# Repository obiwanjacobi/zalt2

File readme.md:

# Zalt II

The design of the Zalt II computer hinges on a 10-slot (PC) ISA powered backplane I had laying around.

So all modules have an ISA edge connector and although the physical construction is the same as the (PC) ISA bus, the electrical connections are different. So don't try plugging the modules into an old PC.

All card modules (except the Main Board) represent a "smart device".
A smart device has it's own processor to give it additional functionality and perform DMA to offload the CPU.

## Main Board v2.0 (manufactured)

The "motherboard" of the Zalt II computer, containing the 20MHz Z80 CPU, a CPLD for condensed system logic (like MMU/MPU) and an MCU for some (serial) peripherals.

---

## Mass Storage Card

> TBD

- Support IDE hard disks / Compact Flash
- Support File System (FAT16/32)
- Efficient file data transfer (DMA and prefetch)

---

## Video Display Card

> TBD

Currently being researched.

We start of with a simple test on an (SSD1963) [LCD display](./Lcd%20display.md) I have.

- command-based interaction
- lots of graphic services (layers, sprites, transformations, animation, scrolling)
- Additional memory for storing graphic assets
- maybe even a built-in windowing system
- VGA and HDMI using a CPLD to do the heavy lifting
- MCU (STM32?) for 'accelerion', additional memory and DMA

---

## Audio Interface Card

> TBD

Fague ideas on what to do here.

- use MIDI (files) to drive the sound generator(s).
- use a teensy and the audio library (design) capabilities as the processor / sound generator.
- Allow samples to be uploaded and played.
- Prepare for recording audio samples (don't make it impossable), but no plans to use it.

---

## Network Card

> TBD

No idea yet how to do this, but seems like a good idea.

- LAN + WIFI (+BLE?)
- W5500 LAN module (AliExpress)

---

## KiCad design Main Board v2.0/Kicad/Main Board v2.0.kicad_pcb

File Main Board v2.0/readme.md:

# Zalt 2

Version 2 of the Zalt homebrew Z80 computer.

## Z80 CPU

The main board runs a 20MHz Z80.

It contains a 512kB ROM and a 512kB RAM.

## Memory Management Unit

- `Page`: a block of 4k of  physical memory that can be freely mapped into the CPU address space.
- `Page Id` (0-8192) an identifier for a memory page from physical memory.
- `Page Index` (0-15) a location for each of the 16 (active) CPU memory pages.
- `Bank`: A collection of assigned `Page Id`s for all `Page Index`es. Only one bank is active at a time and it defines what physical memory pages are visible to the CPU.
- `Bank Id` (0-32): a stack of max 32 banks that are available to the program/task.
- `Map Id` (0-64): allows each task (as in multi-tasking) to have their private stack of (32) banks.

> The ratio between available Bank-Ids and Map-Ids can be changed later if needed.

### Memory Bank Mapping

The CPU memory address is mapped by the MMU to one of the memory pages in physical memory.
This takes the hi-nible of the CPU address to index the lookup table and produce the physical memory address.
Besides the memory address bits, the lookup table also outputs memory-protection bits for each page.

The values in the lookup table can be programmed, thus changing the pages pointed to in the specific page-index locations.

The OS forces one (or more) -at $000- page-index locations to be present in all memory banks.
This ensures that basic machinery for the OS is always accessible for each application memory configuration.

One 4k block of ROM contains only $FF's (RST38). RST38 is a trap instruction to (try to) catch run-away code.
This can be used to map into page-index's where no valid memory is to be configured.

Refer to the OS's [program loader](<./Source/CPU/Program Loader.md>) for more detail on how the 16 page-indexes are allocated.

## Expansion Bus

We are using a powered ISA backplane to make this a modular system.

> After some research I found the goal to keep the ISA bus ISA-compatible -that it would run original PC ISA-cards- to be a great burdon and compilcate the design unnecessary.

This expansion bus definition is different from the (PC) ISA definition, only the Power pins are kept the same.

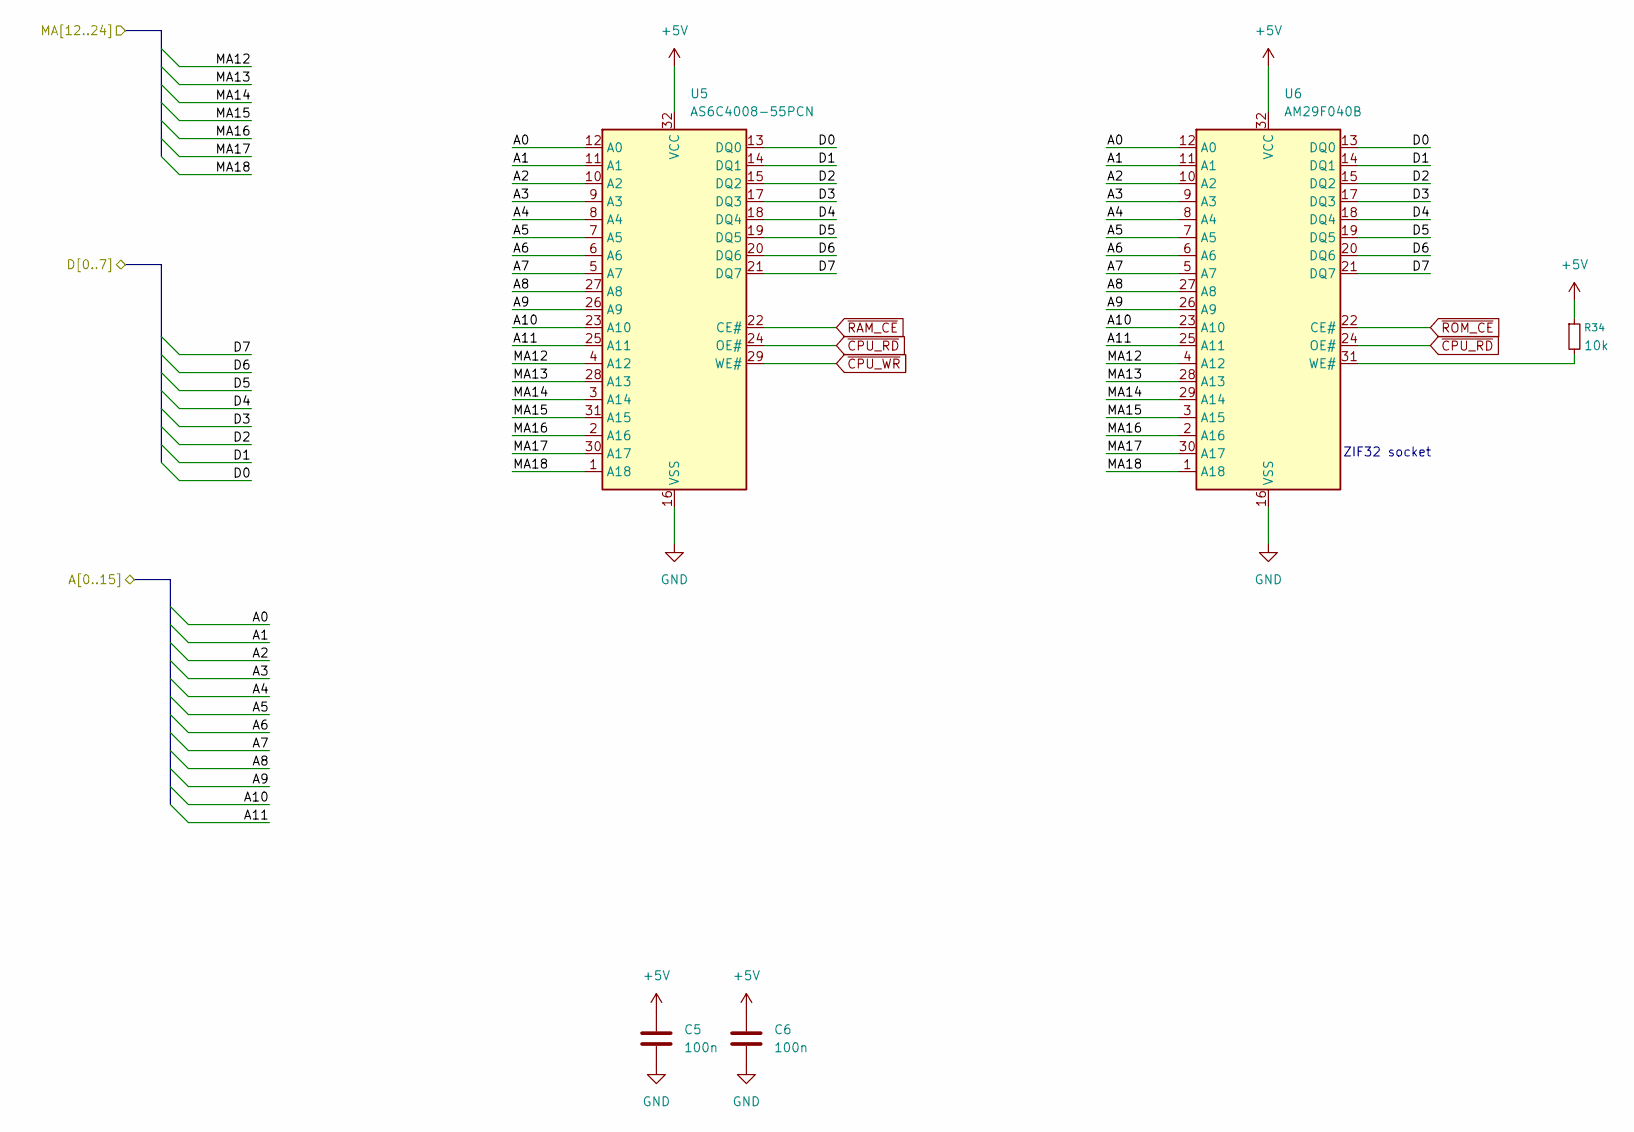
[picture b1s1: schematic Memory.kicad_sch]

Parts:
C5, C6: 100n; C_0603_1608Metric_Pad1.08x0.95mm_HandSolder
R34: 10k; R_0603_1608Metric_Pad0.98x0.95mm_HandSolder
U5: AS6C4008-55PCN; SOP-32_11.305x20.495mm_P1.27mm
U6: AM29F040B; 3M_Textool_232-1288-00-0602J_2x16_P2.54mm

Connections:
+5V: C5.1, C6.1, R34.1, U5.32 (VCC), U6.32 (VCC); also elsewhere on the board
/CPU/A0: U5.12 (A0), U6.12 (A0); also elsewhere on the board
/CPU/A1: U5.11 (A1), U6.11 (A1); also elsewhere on the board
/CPU/A2: U5.10 (A2), U6.10 (A2); also elsewhere on the board
/CPU/A3: U5.9 (A3), U6.9 (A3); also elsewhere on the board
/CPU/A4: U5.8 (A4), U6.8 (A4); also elsewhere on the board
/CPU/A5: U5.7 (A5), U6.7 (A5); also elsewhere on the board
/CPU/A6: U5.6 (A6), U6.6 (A6); also elsewhere on the board
/CPU/A7: U5.5 (A7), U6.5 (A7); also elsewhere on the board
/CPU/A8: U5.27 (A8), U6.27 (A8); also elsewhere on the board
/CPU/A9: U5.26 (A9), U6.26 (A9); also elsewhere on the board
/CPU/A10: U5.23 (A10), U6.23 (A10); also elsewhere on the board
/CPU/A11: U5.25 (A11), U6.25 (A11); also elsewhere on the board
/CPU/D0: U5.13 (DQ0), U6.13 (DQ0); also elsewhere on the board
/CPU/D1: U5.14 (DQ1), U6.14 (DQ1); also elsewhere on the board
/CPU/D2: U5.15 (DQ2), U6.15 (DQ2); also elsewhere on the board
/CPU/D3: U5.17 (DQ3), U6.17 (DQ3); also elsewhere on the board
/CPU/D4: U5.18 (DQ4), U6.18 (DQ4); also elsewhere on the board
/CPU/D5: U5.19 (DQ5), U6.19 (DQ5); also elsewhere on the board
/CPU/D6: U5.20 (DQ6), U6.20 (DQ6); also elsewhere on the board
/CPU/D7: U5.21 (DQ7), U6.21 (DQ7); also elsewhere on the board
/Control Logic/MA12: U5.4 (A12), U6.4 (A12); also elsewhere on the board
/Control Logic/MA13: U5.28 (A13), U6.28 (A13); also elsewhere on the board
/Control Logic/MA14: U5.3 (A14), U6.29 (A14); also elsewhere on the board
/Control Logic/MA15: U5.31 (A15), U6.3 (A15); also elsewhere on the board
/Control Logic/MA16: U5.2 (A16), U6.2 (A16); also elsewhere on the board
/Control Logic/MA17: U5.30 (A17), U6.30 (A17); also elsewhere on the board
/Control Logic/MA18: U5.1 (A18), U6.1 (A18); also elsewhere on the board
GND: C5.2, C6.2, U5.16 (VSS), U6.16 (VSS); also elsewhere on the board
unnamed: R34.2, U6.31 (WE#)
~CPU_RD: U5.24 (OE#), U6.24 (OE#); also elsewhere on the board
~CPU_WR: U5.29 (WE#); also elsewhere on the board
~RAM_CE: U5.22 (CE#); also elsewhere on the board
~ROM_CE: U6.22 (CE#); also elsewhere on the board

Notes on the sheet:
ZIF32 socket

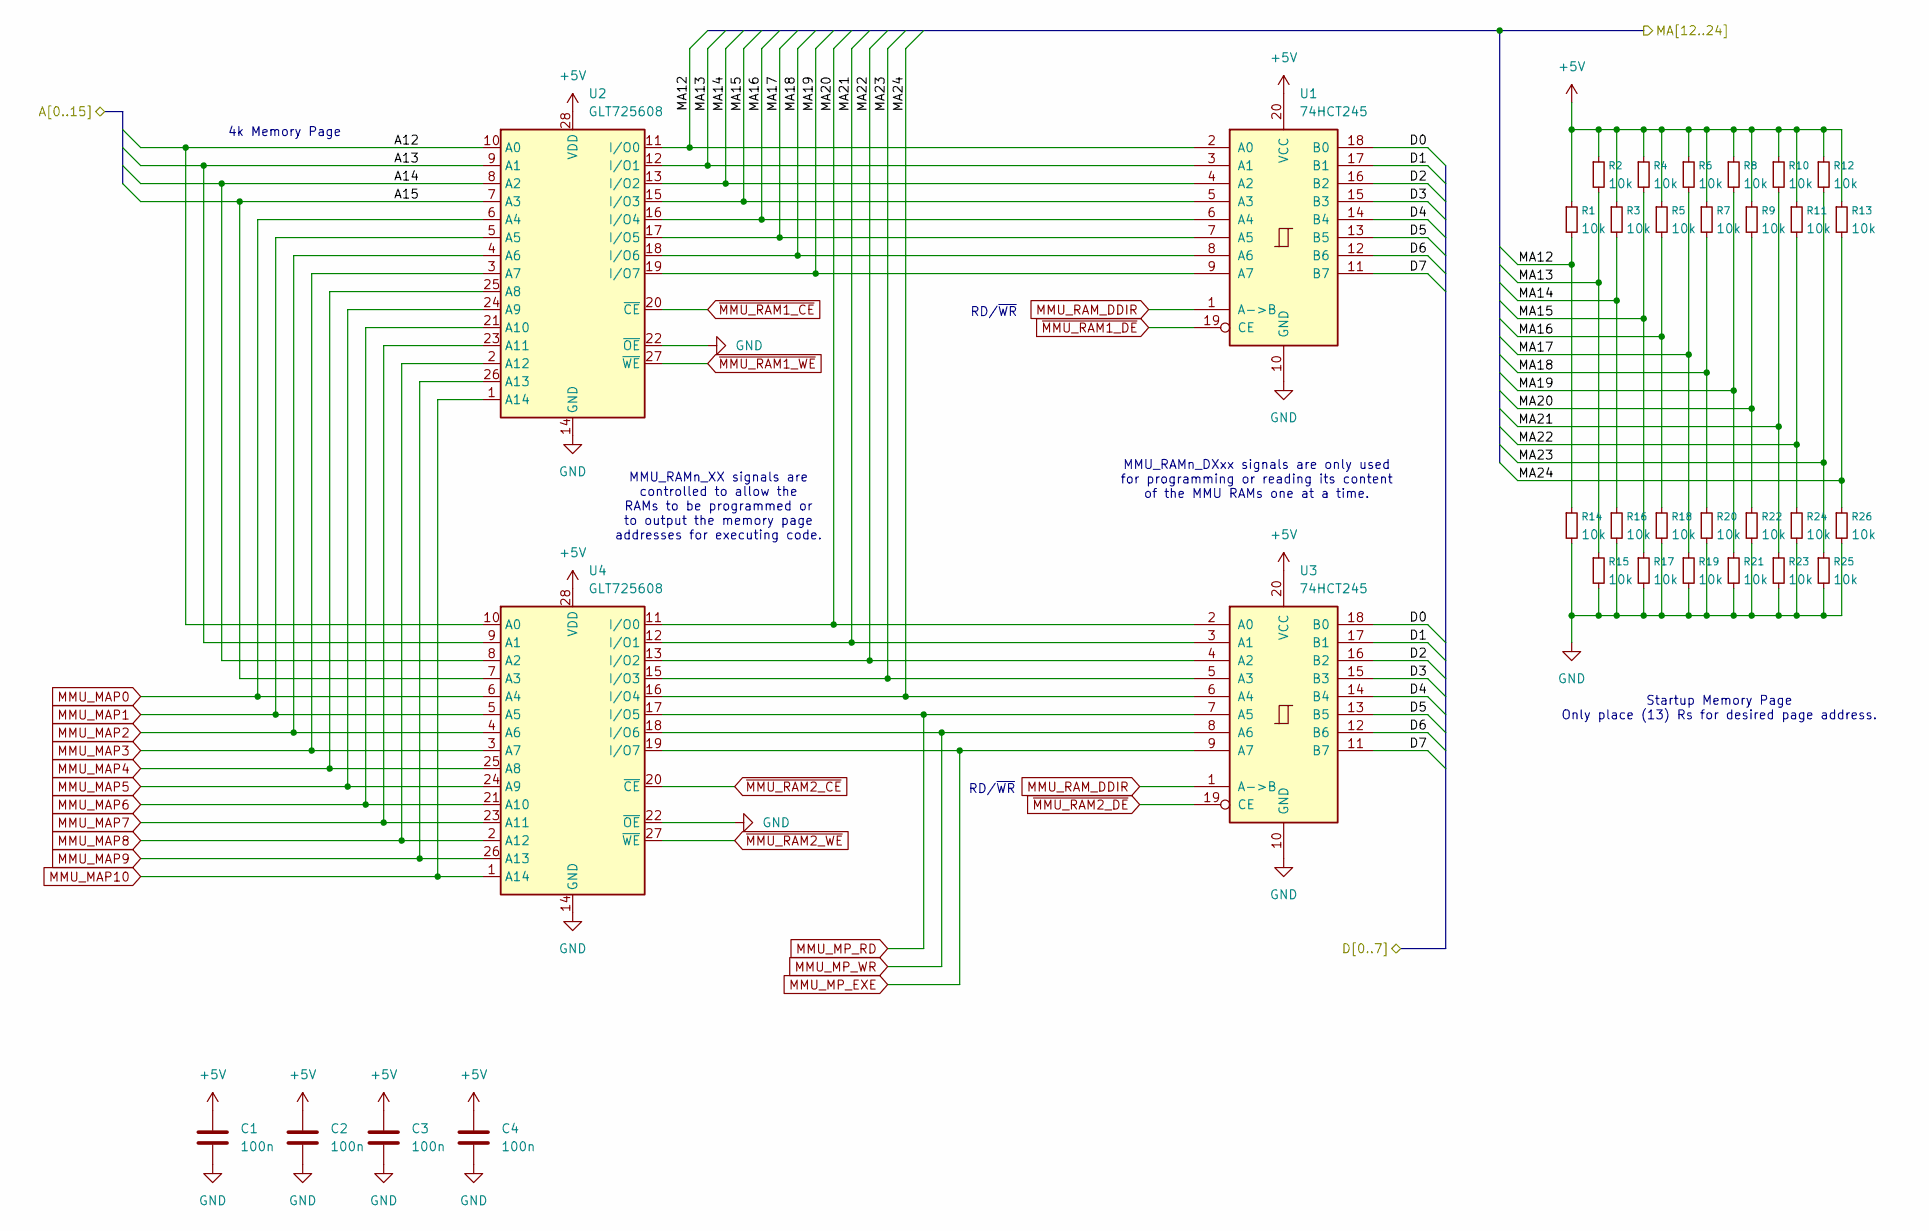
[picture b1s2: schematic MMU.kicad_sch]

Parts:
C1, C2, C3, C4: 100n; C_0603_1608Metric_Pad1.08x0.95mm_HandSolder
R1, R2, R3, R4, R5, R6, R7, R8, R9, R10, R11, R12, R13, R14, R15, R16, R17, R18, R19, R20, R21, R22, R23, R24, R25, R26: 10k; R_0603_1608Metric_Pad0.98x0.95mm_HandSolder
U1, U3: 74HCT245; DIP-20_W7.62mm_Socket_LongNarrowPads
U2, U4: GLT725608; SOJ-28_7.62x18.415mm_P1.27mm

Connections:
+5V: C1.1, C2.1, C3.1, C4.1, R1.1, R2.1, R3.1, R4.1, R5.1, R6.1, R7.1, R8.1, R9.1, R10.1, R11.1, R12.1, R13.1, U1.20 (VCC), U2.28 (VDD), U3.20 (VCC), U4.28 (VDD); also elsewhere on the board
/CPU/A12: U2.10 (A0), U4.10 (A0); also elsewhere on the board
/CPU/A13: U2.9 (A1), U4.9 (A1); also elsewhere on the board
/CPU/A14: U2.8 (A2), U4.8 (A2); also elsewhere on the board
/CPU/A15: U2.7 (A3), U4.7 (A3); also elsewhere on the board
/CPU/D0: U1.18 (B0), U3.18 (B0); also elsewhere on the board
/CPU/D1: U1.17 (B1), U3.17 (B1); also elsewhere on the board
/CPU/D2: U1.16 (B2), U3.16 (B2); also elsewhere on the board
/CPU/D3: U1.15 (B3), U3.15 (B3); also elsewhere on the board
/CPU/D4: U1.14 (B4), U3.14 (B4); also elsewhere on the board
/CPU/D5: U1.13 (B5), U3.13 (B5); also elsewhere on the board
/CPU/D6: U1.12 (B6), U3.12 (B6); also elsewhere on the board
/CPU/D7: U1.11 (B7), U3.11 (B7); also elsewhere on the board
/Control Logic/MA12: R1.2, R14.1, U1.2 (A0), U2.11 (I/O0); also elsewhere on the board
/Control Logic/MA13: R2.2, R15.1, U1.3 (A1), U2.12 (I/O1); also elsewhere on the board
/Control Logic/MA14: R3.2, R16.1, U1.4 (A2), U2.13 (I/O2); also elsewhere on the board
/Control Logic/MA15: R4.2, R17.1, U1.5 (A3), U2.15 (I/O3); also elsewhere on the board
/Control Logic/MA16: R5.2, R18.1, U1.6 (A4), U2.16 (I/O4); also elsewhere on the board
/Control Logic/MA17: R6.2, R19.1, U1.7 (A5), U2.17 (I/O5); also elsewhere on the board
/Control Logic/MA18: R7.2, R20.1, U1.8 (A6), U2.18 (I/O6); also elsewhere on the board
/Control Logic/MA19: R8.2, R21.1, U1.9 (A7), U2.19 (I/O7); also elsewhere on the board
/Control Logic/MA20: R9.2, R22.1, U3.2 (A0), U4.11 (I/O0); also elsewhere on the board
/Control Logic/MA21: R10.2, R23.1, U3.3 (A1), U4.12 (I/O1); also elsewhere on the board
/Control Logic/MA22: R11.2, R24.1, U3.4 (A2), U4.13 (I/O2); also elsewhere on the board
/Control Logic/MA23: R12.2, R25.1, U3.5 (A3), U4.15 (I/O3); also elsewhere on the board
/Control Logic/MA24: R13.2, R26.1, U3.6 (A4), U4.16 (I/O4); also elsewhere on the board
GND: C1.2, C2.2, C3.2, C4.2, R14.2, R15.2, R16.2, R17.2, R18.2, R19.2, R20.2, R21.2, R22.2, R23.2, R24.2, R25.2, R26.2, U1.10 (GND), U2.14 (GND), U2.22 (~OE), U3.10 (GND), U4.14 (GND), U4.22 (~OE); also elsewhere on the board
MMU_MAP0: U2.6 (A4), U4.6 (A4); also elsewhere on the board
MMU_MAP1: U2.5 (A5), U4.5 (A5); also elsewhere on the board
MMU_MAP2: U2.4 (A6), U4.4 (A6); also elsewhere on the board
MMU_MAP3: U2.3 (A7), U4.3 (A7); also elsewhere on the board
MMU_MAP4: U2.25 (A8), U4.25 (A8); also elsewhere on the board
MMU_MAP5: U2.24 (A9), U4.24 (A9); also elsewhere on the board
MMU_MAP6: U2.21 (A10), U4.21 (A10); also elsewhere on the board
MMU_MAP7: U2.23 (A11), U4.23 (A11); also elsewhere on the board
MMU_MAP8: U2.2 (A12), U4.2 (A12); also elsewhere on the board
MMU_MAP9: U2.26 (A13), U4.26 (A13); also elsewhere on the board
MMU_MAP10: U2.1 (A14), U4.1 (A14); also elsewhere on the board
MMU_MP_EXE: U3.9 (A7), U4.19 (I/O7); also elsewhere on the board
MMU_MP_RD: U3.7 (A5), U4.17 (I/O5); also elsewhere on the board
MMU_MP_WR: U3.8 (A6), U4.18 (I/O6); also elsewhere on the board
MMU_RAM_DDIR: U1.1 (A->B), U3.1 (A->B); also elsewhere on the board
~MMU_RAM1_CE: U2.20 (~CE); also elsewhere on the board
~MMU_RAM1_DE: U1.19 (CE); also elsewhere on the board
~MMU_RAM1_WE: U2.27 (~WE); also elsewhere on the board
~MMU_RAM2_CE: U4.20 (~CE); also elsewhere on the board
~MMU_RAM2_DE: U3.19 (CE); also elsewhere on the board
~MMU_RAM2_WE: U4.27 (~WE); also elsewhere on the board

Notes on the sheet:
RD/~{WR}
MMU_RAMn_DXxx signals are only used for programming or reading its content of the MMU RAMs one at a time.
MMU_RAMn_XX signals are controlled to allow the RAMs to be programmed or to output the memory page addresses for executing code.
4k Memory Page
Startup Memory Page Only place (13) Rs for desired page address.

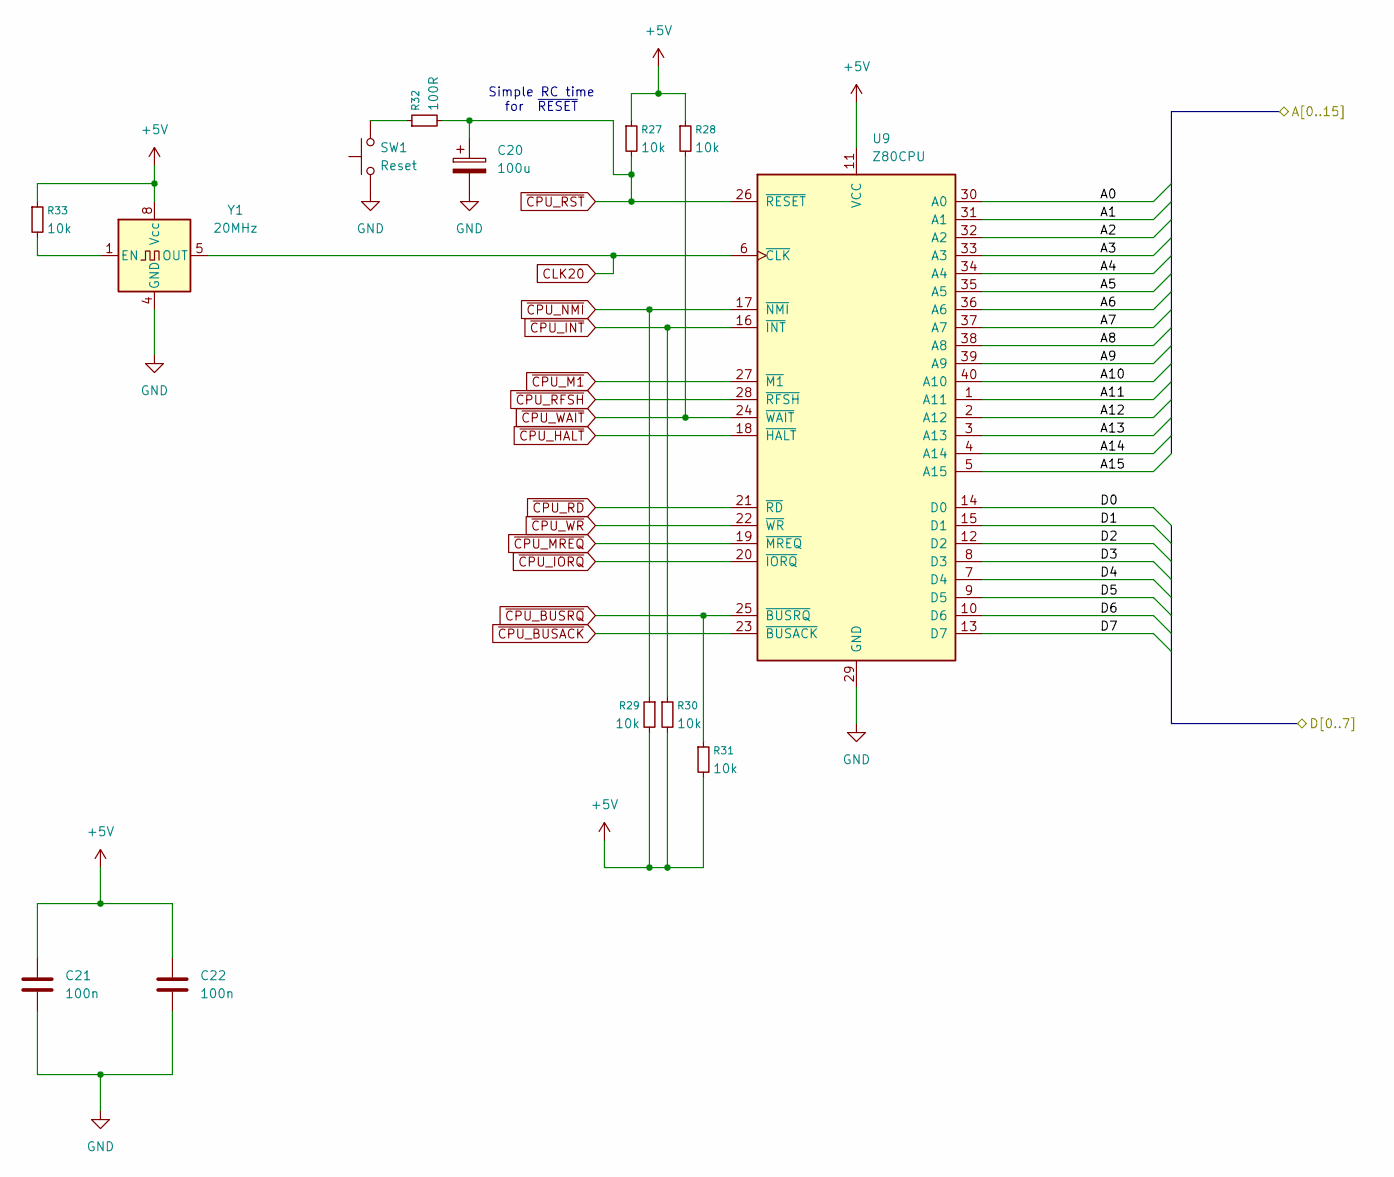
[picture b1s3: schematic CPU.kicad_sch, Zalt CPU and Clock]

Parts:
C20: 100u; CP_Radial_D8.0mm_P3.80mm
C21, C22: 100n; C_0603_1608Metric_Pad1.08x0.95mm_HandSolder
R27, R28, R29, R30, R31, R33: 10k; R_0603_1608Metric_Pad0.98x0.95mm_HandSolder
R32: 100R; R_0603_1608Metric_Pad0.98x0.95mm_HandSolder
SW1: Reset; SW_Tactile_SPST_Angled_PTS645Vx83-2LFS
U9: Z80CPU; 3M_Textool_240-1288-00-0602J_2x20_P2.54mm
Y1: 20MHz; Oscillator_DIP-8_LargePads

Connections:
+5V: C21.1, C22.1, R27.1, R28.1, R29.2, R30.2, R31.2, R33.1, U9.11 (VCC), Y1.8 (Vcc); also elsewhere on the board
/CPU/A0: U9.30 (A0); also elsewhere on the board
/CPU/A1: U9.31 (A1); also elsewhere on the board
/CPU/A2: U9.32 (A2); also elsewhere on the board
/CPU/A3: U9.33 (A3); also elsewhere on the board
/CPU/A4: U9.34 (A4); also elsewhere on the board
/CPU/A5: U9.35 (A5); also elsewhere on the board
/CPU/A6: U9.36 (A6); also elsewhere on the board
/CPU/A7: U9.37 (A7); also elsewhere on the board
/CPU/A8: U9.38 (A8); also elsewhere on the board
/CPU/A9: U9.39 (A9); also elsewhere on the board
/CPU/A10: U9.40 (A10); also elsewhere on the board
/CPU/A11: U9.1 (A11); also elsewhere on the board
/CPU/A12: U9.2 (A12); also elsewhere on the board
/CPU/A13: U9.3 (A13); also elsewhere on the board
/CPU/A14: U9.4 (A14); also elsewhere on the board
/CPU/A15: U9.5 (A15); also elsewhere on the board
/CPU/D0: U9.14 (D0); also elsewhere on the board
/CPU/D1: U9.15 (D1); also elsewhere on the board
/CPU/D2: U9.12 (D2); also elsewhere on the board
/CPU/D3: U9.8 (D3); also elsewhere on the board
/CPU/D4: U9.7 (D4); also elsewhere on the board
/CPU/D5: U9.9 (D5); also elsewhere on the board
/CPU/D6: U9.10 (D6); also elsewhere on the board
/CPU/D7: U9.13 (D7); also elsewhere on the board
CLK20: U9.6 (~CLK), Y1.5 (OUT); also elsewhere on the board
GND: C20.2, C21.2, C22.2, SW1.1, U9.29 (GND), Y1.4 (GND); also elsewhere on the board
unnamed: R32.1, SW1.2
unnamed: R33.2, Y1.1 (EN)
~CPU_BUSACK: U9.23 (~BUSACK); also elsewhere on the board
~CPU_BUSRQ: R31.1, U9.25 (~BUSRQ); also elsewhere on the board
~CPU_HALT: U9.18 (~HALT); also elsewhere on the board
~CPU_INT: R30.1, U9.16 (~INT); also elsewhere on the board
~CPU_IORQ: U9.20 (~IORQ); also elsewhere on the board
~CPU_M1: U9.27 (~M1); also elsewhere on the board
~CPU_MREQ: U9.19 (~MREQ); also elsewhere on the board
~CPU_NMI: R29.1, U9.17 (~NMI); also elsewhere on the board
~CPU_RD: U9.21 (~RD); also elsewhere on the board
~CPU_RFSH: U9.28 (~RFSH); also elsewhere on the board
~CPU_RST: C20.1, R27.2, R32.2, U9.26 (~RESET); also elsewhere on the board
~CPU_WAIT: R28.2, U9.24 (~WAIT); also elsewhere on the board
~CPU_WR: U9.22 (~WR); also elsewhere on the board

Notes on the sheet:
Simple RC time for ~{RESET}

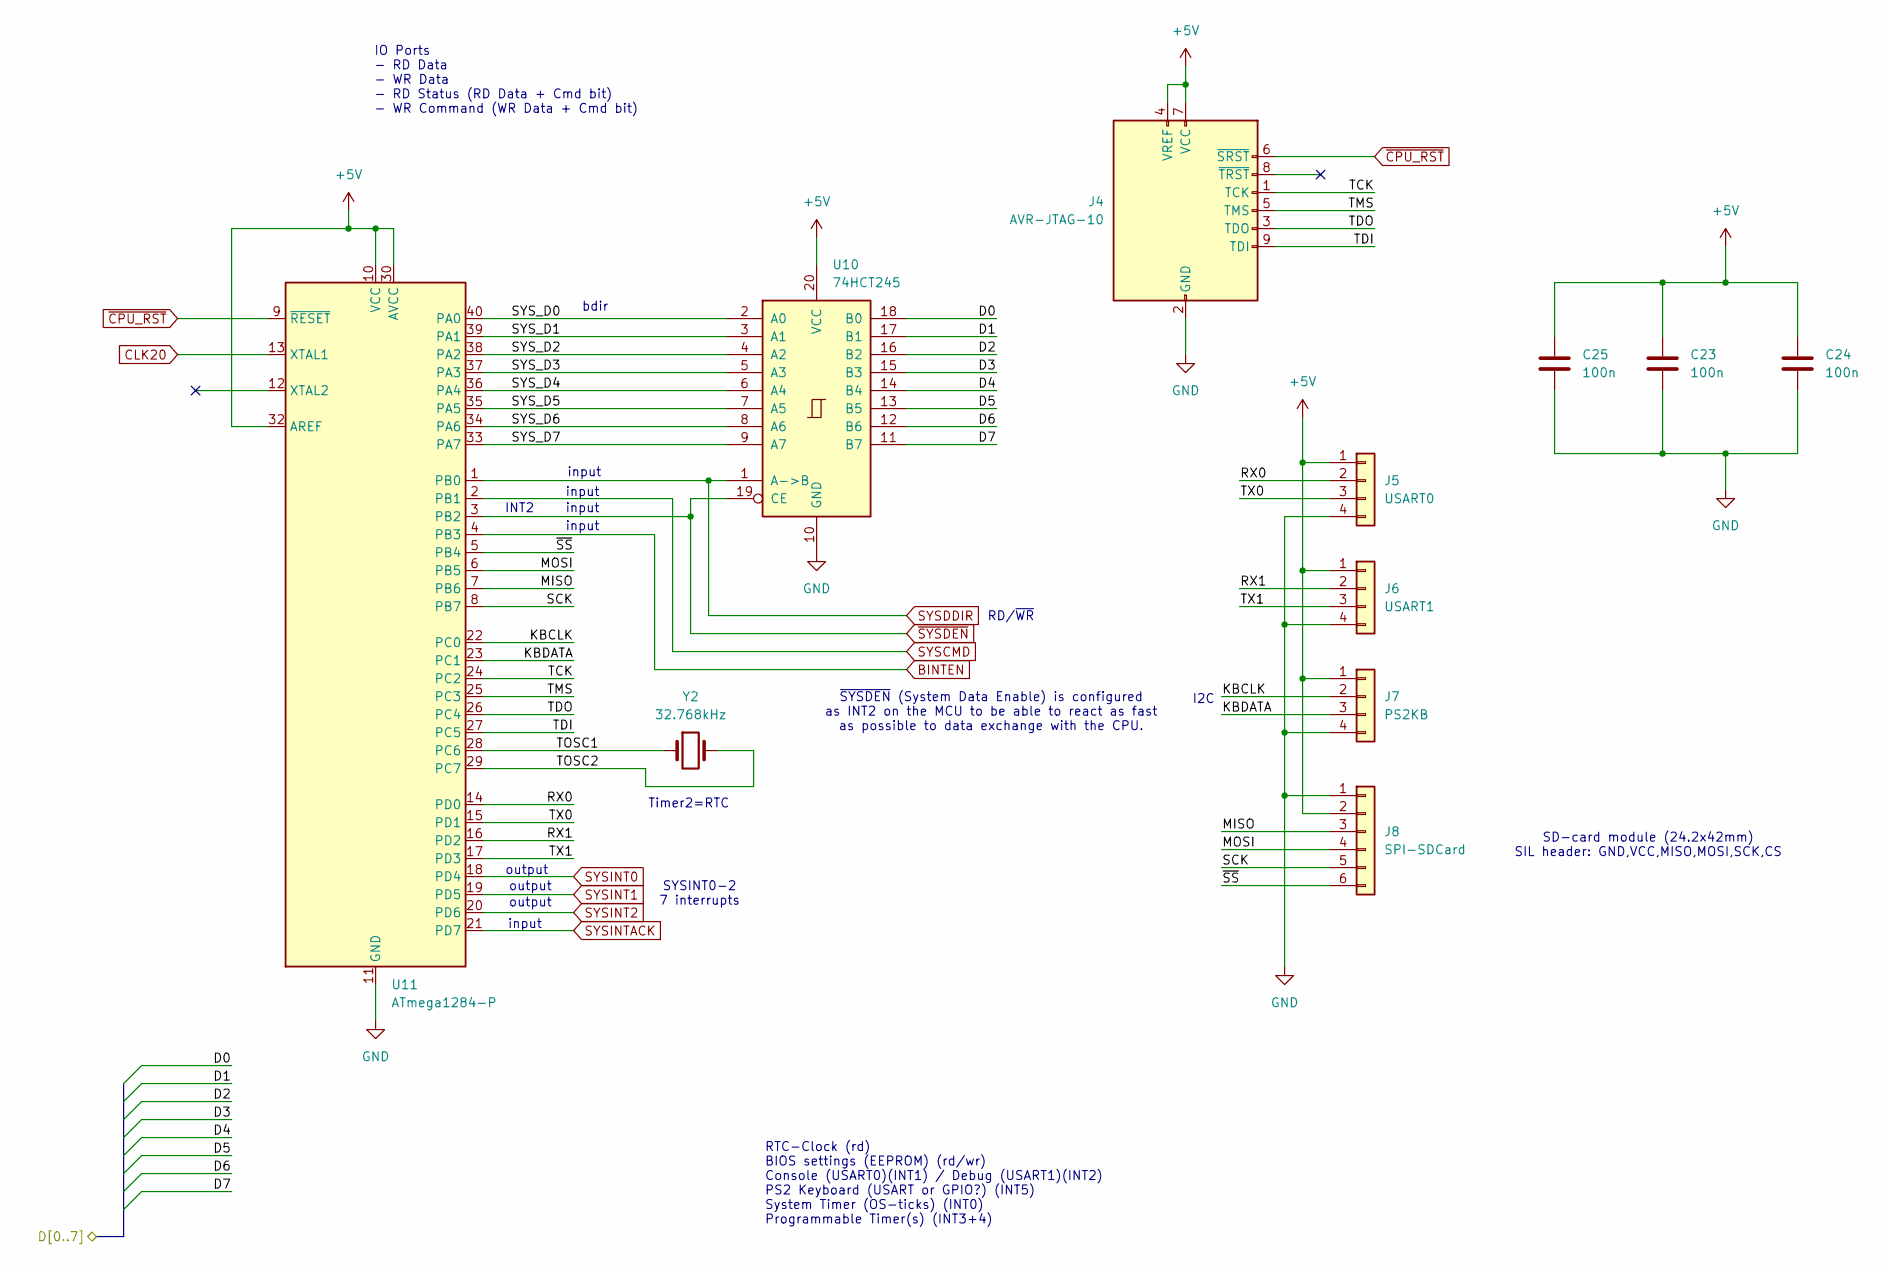
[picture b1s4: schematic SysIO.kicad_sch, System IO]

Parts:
C23, C24, C25: 100n; C_0603_1608Metric_Pad1.08x0.95mm_HandSolder
J4: AVR-JTAG-10; IDC-Header_2x05_P2.54mm_Vertical
J5: USART0; PinHeader_1x04_P2.54mm_Vertical
J6: USART1; PinHeader_1x04_P2.54mm_Vertical
J7: PS2KB; PinHeader_1x04_P2.54mm_Vertical
J8: SPI-SDCard; PinSocket_1x06_P2.54mm_Vertical
U10: 74HCT245; DIP-20_W7.62mm_Socket_LongNarrowPads
U11: ATmega1284-P; DIP-40_W15.24mm_Socket_LongPads
Y2: 32.768kHz; Crystal_C26-LF_D2.1mm_L6.5mm_Horizontal

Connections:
+5V: C23.1, C24.1, C25.1, J4.4 (VREF), J4.7 (VCC), J5.1, J6.1, J7.1, J8.2, U10.20 (VCC), U11.10 (VCC), U11.30 (AVCC), U11.32 (AREF); also elsewhere on the board
/CPU/D0: U10.18 (B0); also elsewhere on the board
/CPU/D1: U10.17 (B1); also elsewhere on the board
/CPU/D2: U10.16 (B2); also elsewhere on the board
/CPU/D3: U10.15 (B3); also elsewhere on the board
/CPU/D4: U10.14 (B4); also elsewhere on the board
/CPU/D5: U10.13 (B5); also elsewhere on the board
/CPU/D6: U10.12 (B6); also elsewhere on the board
/CPU/D7: U10.11 (B7); also elsewhere on the board
/SysIO/KBCLK: J7.2, U11.22 (PC0)
/SysIO/KBDATA: J7.3, U11.23 (PC1)
/SysIO/MISO: J8.3, U11.7 (PB6)
/SysIO/MOSI: J8.4, U11.6 (PB5)
/SysIO/RX0: J5.2, U11.14 (PD0)
/SysIO/RX1: J6.2, U11.16 (PD2)
/SysIO/SCK: J8.5, U11.8 (PB7)
/SysIO/SYS_D0: U10.2 (A0), U11.40 (PA0)
/SysIO/SYS_D1: U10.3 (A1), U11.39 (PA1)
/SysIO/SYS_D2: U10.4 (A2), U11.38 (PA2)
/SysIO/SYS_D3: U10.5 (A3), U11.37 (PA3)
/SysIO/SYS_D4: U10.6 (A4), U11.36 (PA4)
/SysIO/SYS_D5: U10.7 (A5), U11.35 (PA5)
/SysIO/SYS_D6: U10.8 (A6), U11.34 (PA6)
/SysIO/SYS_D7: U10.9 (A7), U11.33 (PA7)
/SysIO/TCK: J4.1 (TCK), U11.24 (PC2)
/SysIO/TDI: J4.9 (TDI), U11.27 (PC5)
/SysIO/TDO: J4.3 (TDO), U11.26 (PC4)
/SysIO/TMS: J4.5 (TMS), U11.25 (PC3)
/SysIO/TOSC1: U11.28 (PC6), Y2.1
/SysIO/TOSC2: U11.29 (PC7), Y2.2
/SysIO/TX0: J5.3, U11.15 (PD1)
/SysIO/TX1: J6.3, U11.17 (PD3)
/SysIO/~SS: J8.6, U11.5 (PB4)
BINTEN: U11.4 (PB3); also elsewhere on the board
CLK20: U11.13 (XTAL1); also elsewhere on the board
GND: C23.2, C24.2, C25.2, J4.2 (GND), J4.10 (GND), J5.4, J6.4, J7.4, J8.1, U10.10 (GND), U11.11 (GND), U11.31 (GND); also elsewhere on the board
SYSCMD: U11.2 (PB1); also elsewhere on the board
SYSDDIR: U10.1 (A->B), U11.1 (PB0); also elsewhere on the board
SYSINT0: U11.18 (PD4); also elsewhere on the board
SYSINT1: U11.19 (PD5); also elsewhere on the board
SYSINT2: U11.20 (PD6); also elsewhere on the board
SYSINTACK: U11.21 (PD7); also elsewhere on the board
~CPU_RST: J4.6 (~SRST), U11.9 (~RESET); also elsewhere on the board
~SYSDEN: U10.19 (CE), U11.3 (PB2); also elsewhere on the board

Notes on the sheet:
IO Ports - RD Data - WR Data - RD Status (RD Data + Cmd bit) - WR Command (WR Data + Cmd bit)
output
RTC-Clock (rd) BIOS settings (EEPROM) (rd/wr) Console (USART0)(INT1) / Debug (USART1)(INT2) PS2 Keyboard (USART or GPIO?) (INT5) System Timer (OS-ticks) (INT0) Programmable Timer(s) (INT3+4)
input
bdir
SYSINT0-2 7 interrupts
~{SYSDEN} (System Data Enable) is configured as INT2 on the MCU to be able to react as fast as possible to data exchange with the CPU.
I2C
Timer2=RTC
INT2
SD-card module (24.2x42mm) SIL header: GND,VCC,MISO,MOSI,SCK,CS
RD/~{WR}

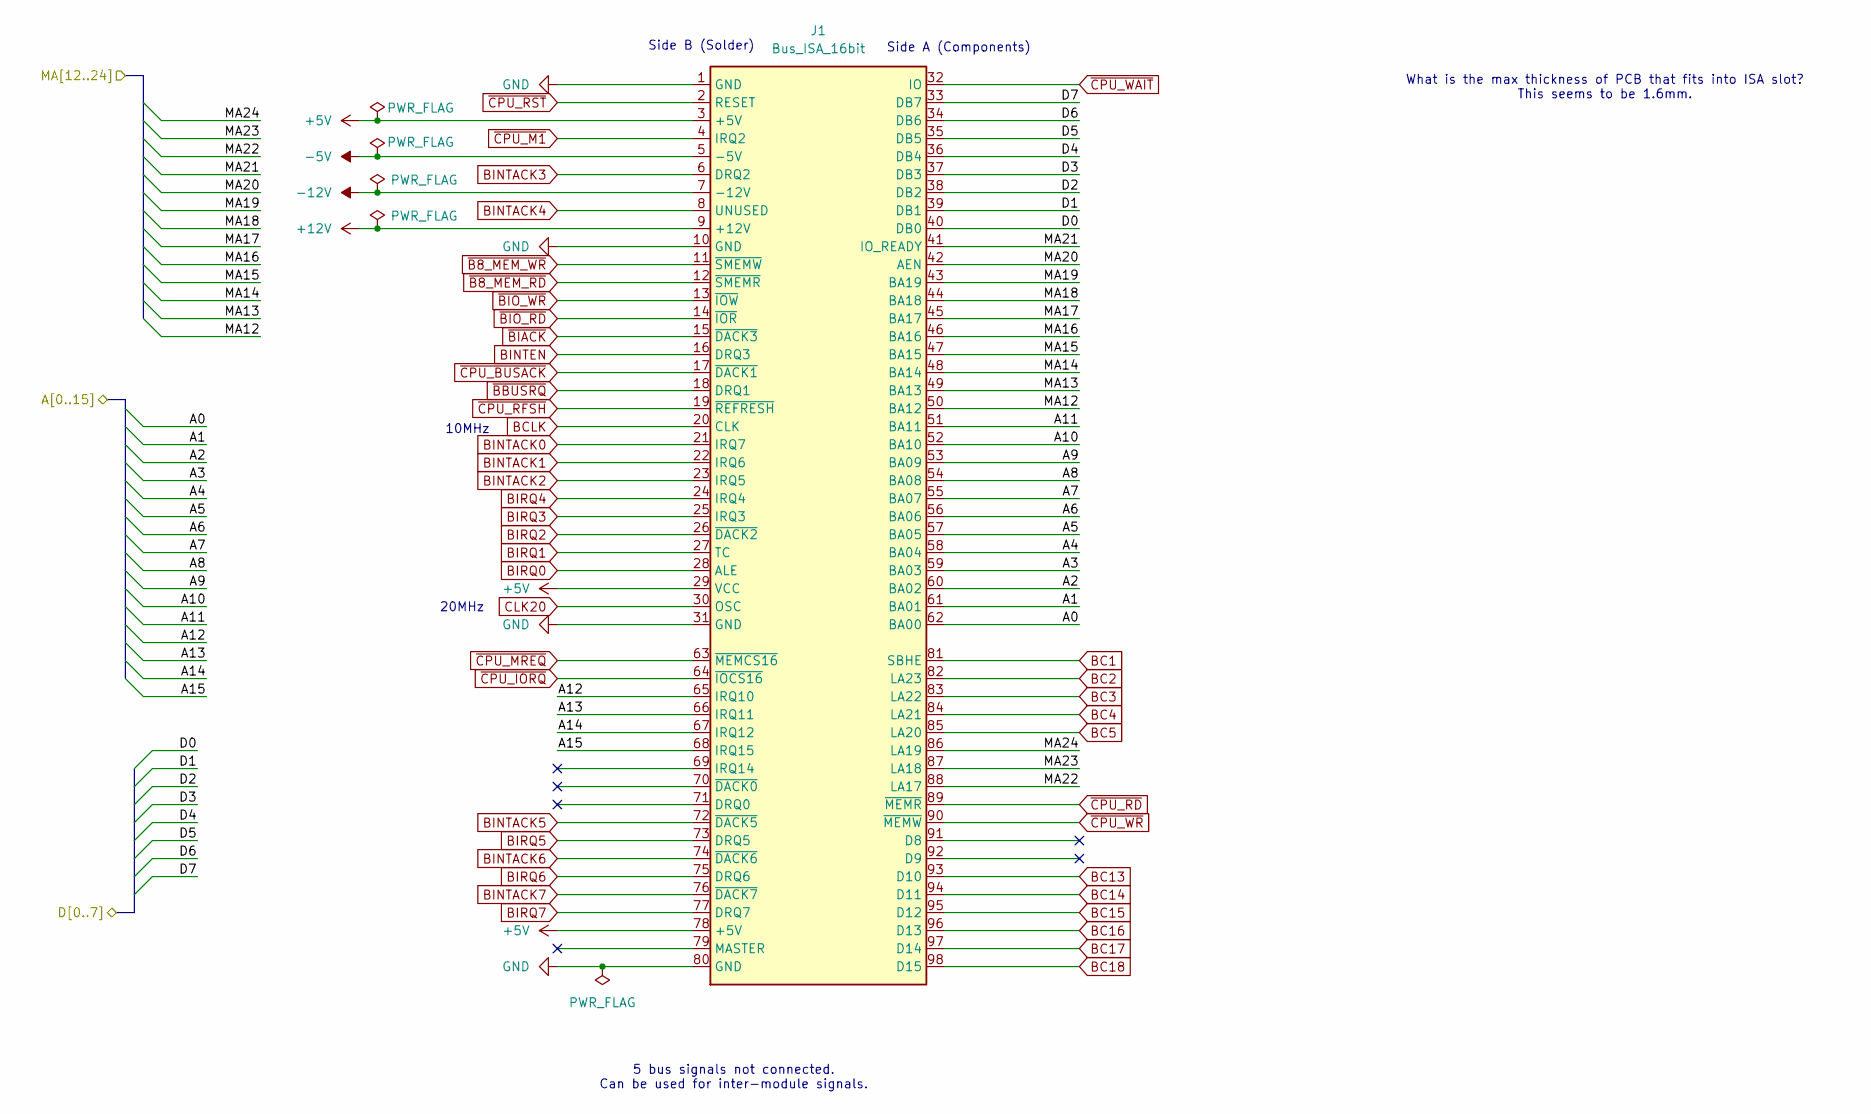
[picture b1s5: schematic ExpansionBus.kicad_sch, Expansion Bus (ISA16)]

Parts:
J1: Bus_ISA_16bit; BUS_AT

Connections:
+5V: J1.3 (+5V), J1.29 (VCC), J1.78 (+5V); also elsewhere on the board
+12V: J1.9 (+12V)
-5V: J1.5 (-5V)
-12V: J1.7 (-12V)
/CPU/A0: J1.62 (BA00); also elsewhere on the board
/CPU/A1: J1.61 (BA01); also elsewhere on the board
/CPU/A2: J1.60 (BA02); also elsewhere on the board
/CPU/A3: J1.59 (BA03); also elsewhere on the board
/CPU/A4: J1.58 (BA04); also elsewhere on the board
/CPU/A5: J1.57 (BA05); also elsewhere on the board
/CPU/A6: J1.56 (BA06); also elsewhere on the board
/CPU/A7: J1.55 (BA07); also elsewhere on the board
/CPU/A8: J1.54 (BA08); also elsewhere on the board
/CPU/A9: J1.53 (BA09); also elsewhere on the board
/CPU/A10: J1.52 (BA10); also elsewhere on the board
/CPU/A11: J1.51 (BA11); also elsewhere on the board
/CPU/A12: J1.65 (IRQ10); also elsewhere on the board
/CPU/A13: J1.66 (IRQ11); also elsewhere on the board
/CPU/A14: J1.67 (IRQ12); also elsewhere on the board
/CPU/A15: J1.68 (IRQ15); also elsewhere on the board
/CPU/D0: J1.40 (DB0); also elsewhere on the board
/CPU/D1: J1.39 (DB1); also elsewhere on the board
/CPU/D2: J1.38 (DB2); also elsewhere on the board
/CPU/D3: J1.37 (DB3); also elsewhere on the board
/CPU/D4: J1.36 (DB4); also elsewhere on the board
/CPU/D5: J1.35 (DB5); also elsewhere on the board
/CPU/D6: J1.34 (DB6); also elsewhere on the board
/CPU/D7: J1.33 (DB7); also elsewhere on the board
/Control Logic/MA12: J1.50 (BA12); also elsewhere on the board
/Control Logic/MA13: J1.49 (BA13); also elsewhere on the board
/Control Logic/MA14: J1.48 (BA14); also elsewhere on the board
/Control Logic/MA15: J1.47 (BA15); also elsewhere on the board
/Control Logic/MA16: J1.46 (BA16); also elsewhere on the board
/Control Logic/MA17: J1.45 (BA17); also elsewhere on the board
/Control Logic/MA18: J1.44 (BA18); also elsewhere on the board
/Control Logic/MA19: J1.43 (BA19); also elsewhere on the board
/Control Logic/MA20: J1.42 (AEN); also elsewhere on the board
/Control Logic/MA21: J1.41 (IO_READY); also elsewhere on the board
/Control Logic/MA22: J1.88 (LA17); also elsewhere on the board
/Control Logic/MA23: J1.87 (LA18); also elsewhere on the board
/Control Logic/MA24: J1.86 (LA19); also elsewhere on the board
BC1: J1.81 (SBHE); also elsewhere on the board
BC2: J1.82 (LA23); also elsewhere on the board
BC3: J1.83 (LA22); also elsewhere on the board
BC4: J1.84 (LA21); also elsewhere on the board
BC5: J1.85 (LA20); also elsewhere on the board
BC13: J1.93 (D10); also elsewhere on the board
BC14: J1.94 (D11); also elsewhere on the board
BC15: J1.95 (D12); also elsewhere on the board
BC16: J1.96 (D13); also elsewhere on the board
BC17: J1.97 (D14); also elsewhere on the board
BC18: J1.98 (D15); also elsewhere on the board
BCLK: J1.20 (CLK); also elsewhere on the board
BINTACK0: J1.21 (IRQ7); also elsewhere on the board
BINTACK1: J1.22 (IRQ6); also elsewhere on the board
BINTACK2: J1.23 (IRQ5); also elsewhere on the board
BINTACK3: J1.6 (DRQ2); also elsewhere on the board
BINTACK4: J1.8 (UNUSED); also elsewhere on the board
BINTACK5: J1.72 (~DACK5); also elsewhere on the board
BINTACK6: J1.74 (~DACK6); also elsewhere on the board
BINTACK7: J1.76 (~DACK7); also elsewhere on the board
BINTEN: J1.16 (DRQ3); also elsewhere on the board
BIRQ0: J1.28 (ALE); also elsewhere on the board
BIRQ1: J1.27 (TC); also elsewhere on the board
BIRQ2: J1.26 (~DACK2); also elsewhere on the board
BIRQ3: J1.25 (IRQ3); also elsewhere on the board
BIRQ4: J1.24 (IRQ4); also elsewhere on the board
BIRQ5: J1.73 (DRQ5); also elsewhere on the board
BIRQ6: J1.75 (DRQ6); also elsewhere on the board
BIRQ7: J1.77 (DRQ7); also elsewhere on the board
CLK20: J1.30 (OSC); also elsewhere on the board
GND: J1.1 (GND), J1.10 (GND), J1.31 (GND), J1.80 (GND); also elsewhere on the board
~B8_MEM_RD: J1.12 (~SMEMR); also elsewhere on the board
~B8_MEM_WR: J1.11 (~SMEMW); also elsewhere on the board
~BBUSRQ: J1.18 (DRQ1); also elsewhere on the board
~BIACK: J1.15 (~DACK3); also elsewhere on the board
~BIO_RD: J1.14 (~IOR); also elsewhere on the board
~BIO_WR: J1.13 (~IOW); also elsewhere on the board
~CPU_BUSACK: J1.17 (~DACK1); also elsewhere on the board
~CPU_IORQ: J1.64 (~IOCS16); also elsewhere on the board
~CPU_M1: J1.4 (IRQ2); also elsewhere on the board
~CPU_MREQ: J1.63 (~MEMCS16); also elsewhere on the board
~CPU_RD: J1.89 (~MEMR); also elsewhere on the board
~CPU_RFSH: J1.19 (~REFRESH); also elsewhere on the board
~CPU_RST: J1.2 (RESET); also elsewhere on the board
~CPU_WAIT: J1.32 (IO); also elsewhere on the board
~CPU_WR: J1.90 (~MEMW); also elsewhere on the board

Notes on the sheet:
Side B (Solder)
5 bus signals not connected. Can be used for inter-module signals.
Side A (Components)
What is the max thickness of PCB that fits into ISA slot? This seems to be 1.6mm.
20MHz
10MHz
